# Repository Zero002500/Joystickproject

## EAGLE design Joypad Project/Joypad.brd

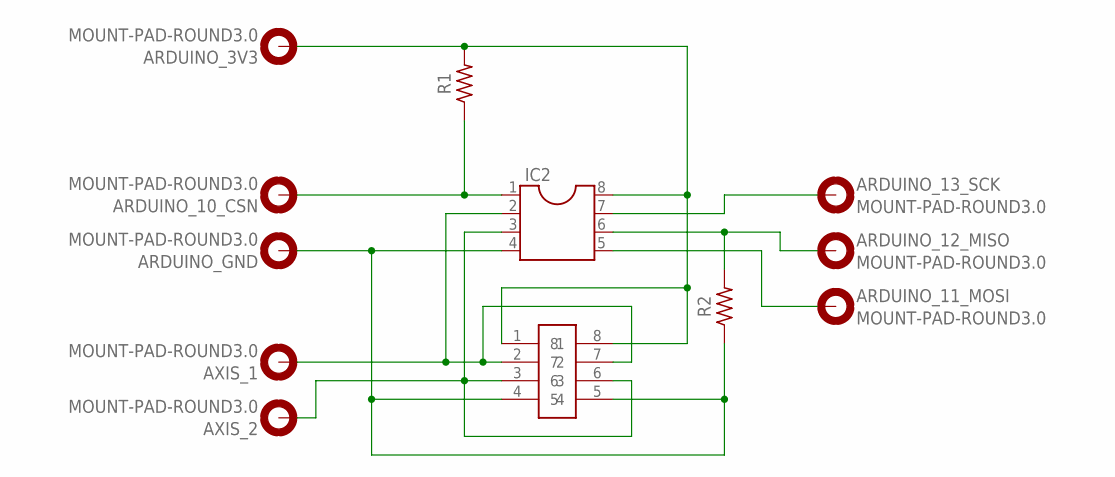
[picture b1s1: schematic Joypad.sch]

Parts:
ARDUINO_3V3, ARDUINO_10_CSN, ARDUINO_11_MOSI, ARDUINO_12_MISO, ARDUINO_13_SCK: MOUNT-PAD-ROUND3.0; 3,0-PAD
ARDUINO_GND: MOUNT-PAD-ROUND3.0; 3,0-PAD
AXIS_1, AXIS_2: MOUNT-PAD-ROUND3.0; 3,0-PAD
IC2: DIL8S; SOCKET-08
R1, R2: R-US_AXIAL-7.2MM-PITCH; RESAD724W46L381D178B
U$1: JOYSTICK

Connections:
unnamed: AXIS_1.B3,0, IC2.2, U$1.2, U$1.7
unnamed: AXIS_2.B3,0, IC2.3, U$1.3, U$1.6
unnamed: ARDUINO_12_MISO.B3,0, IC2.6, R2.2
unnamed: ARDUINO_3V3.B3,0, IC2.8, R1.2, U$1.1, U$1.8
unnamed: ARDUINO_10_CSN.B3,0, IC2.1, R1.1
unnamed: ARDUINO_13_SCK.B3,0, IC2.7
unnamed: ARDUINO_11_MOSI.B3,0, IC2.5
unnamed: ARDUINO_GND.B3,0, IC2.4, R2.1, U$1.4, U$1.5

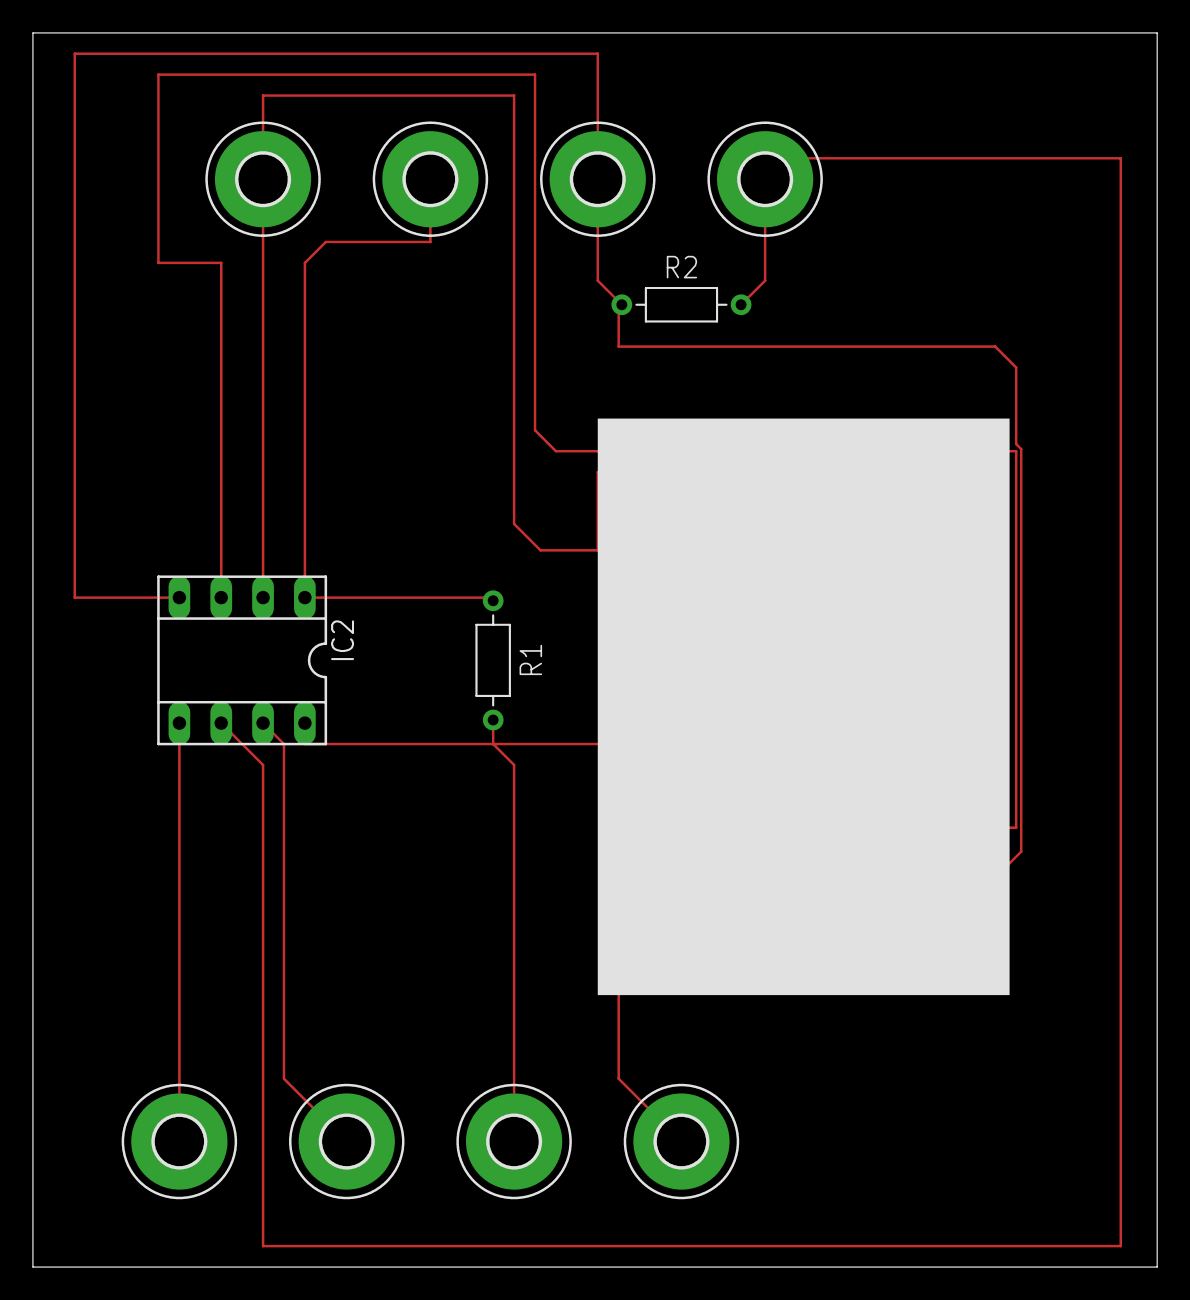
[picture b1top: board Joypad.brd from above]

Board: 2 copper layers, 68.2 x 74.9 mm, 12 parts (0 on the bottom side), 8 nets.
